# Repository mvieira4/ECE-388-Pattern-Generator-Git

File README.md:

# ECE-388-Pattern-Generator-Git
Demo https://youtu.be/JeO_5P8q-XI

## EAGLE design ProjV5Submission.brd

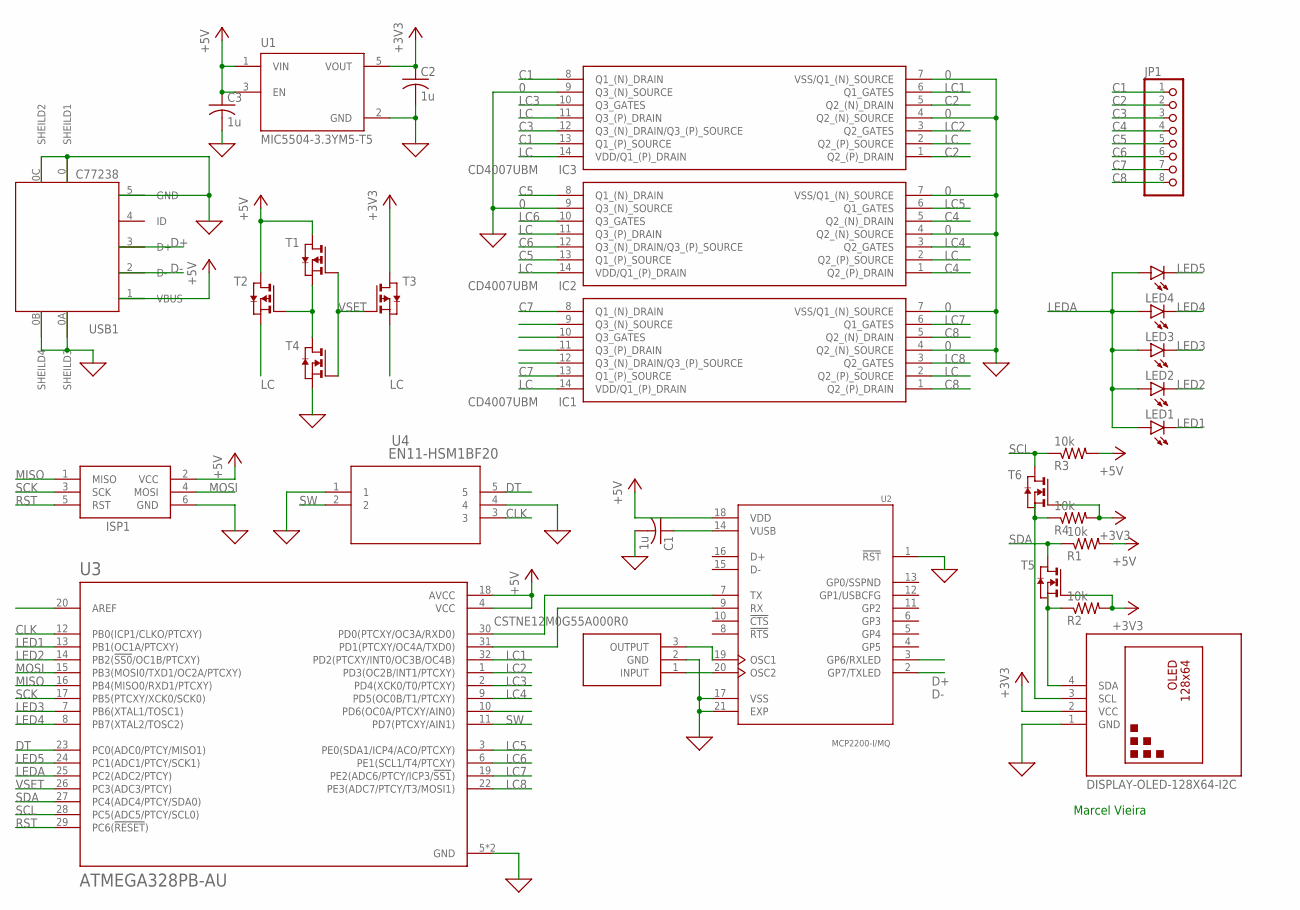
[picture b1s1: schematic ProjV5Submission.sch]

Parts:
C1, C2, C3: 1u; C0805
IC1, IC2, IC3: CD4007UBM; SOIC127P600X175-14N
ISP1: AVRISP-6; AVRISP
JP1: PINHD-1X8-3.5MM; 1X08-3.5MM
LED1, LED2, LED3, LED4, LED5: LEDCHIP-LED0805; CHIP-LED0805
R1, R2, R3, R4: 10k; R0805
T1, T2, T3: PMOSSOT23; SOT-23
T4, T5, T6: NMOSSOT23; SOT-23
U1: MIC5504-3.3YM5-T5; SOT95P280X145-5N
U2: MCP2200-I/MQ; QFN65P500X500X100-21N
U3: ATMEGA328PB-AU; QFP80P900X900X120-32N
U4: EN11-HSM1BF20; EN11-HSM_TTE
U$1: DISPLAY-OLED-128X64-I2C
USB1: C77238
Y1: CSTNE12M0G55A000R0

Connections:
0: C1.2, C2.2, C3.2, IC1.4 (Q2_(N)_SOURCE), IC1.7 (VSS/Q1_(N)_SOURCE), IC2.4 (Q2_(N)_SOURCE), IC2.7 (VSS/Q1_(N)_SOURCE), IC2.9 (Q3_(N)_SOURCE), IC3.4 (Q2_(N)_SOURCE), IC3.7 (VSS/Q1_(N)_SOURCE), IC3.9 (Q3_(N)_SOURCE), ISP1.6 (GND), T4.2 (S), U1.2 (GND), U2.1 (!RST), U2.17 (VSS), U2.21 (EXP), U3.5 (GND), U3.21 (GND), U4.1, U4.4, U$1.1 (GND), USB1.0 (SHEILD1), USB1.0A (SHEILD3), USB1.0B (SHEILD4), USB1.0C (SHEILD2), USB1.5 (GND), Y1.2 (GND)
+3V3: C2.1, R2.2, R4.2, T3.1 (D), T5.3 (G), T6.3 (G), U1.5 (VOUT), U$1.2 (VCC)
+5V: C3.1, ISP1.2 (VCC), R1.2, R3.2, T1.1 (D), T2.1 (D), U1.1 (VIN), U1.3 (EN), U2.18 (VDD), U3.4 (VCC), U3.18 (AVCC), USB1.1 (VBUS)
C1: IC3.8 (Q1_(N)_DRAIN), IC3.13 (Q1_(P)_SOURCE), JP1.1
C2: IC3.1 (Q2_(P)_DRAIN), IC3.5 (Q2_(N)_DRAIN), JP1.2
C3: IC3.12 (Q3_(N)_DRAIN/Q3_(P)_SOURCE), JP1.3
C4: IC2.1 (Q2_(P)_DRAIN), IC2.5 (Q2_(N)_DRAIN), JP1.4
C5: IC2.8 (Q1_(N)_DRAIN), IC2.13 (Q1_(P)_SOURCE), JP1.5
C6: IC2.12 (Q3_(N)_DRAIN/Q3_(P)_SOURCE), JP1.6
C7: IC1.8 (Q1_(N)_DRAIN), IC1.13 (Q1_(P)_SOURCE), JP1.7
C8: IC1.1 (Q2_(P)_DRAIN), IC1.5 (Q2_(N)_DRAIN), JP1.8
CLK: U3.12 (PB0(ICP1/CLKO/PTCXY)), U4.3
D+: U2.3 (GP6/RXLED), USB1.3 (D+)
D-: U2.2 (GP7/TXLED), USB1.2 (D-)
DT: U3.23 (PC0(ADC0/PTCY/MISO1)), U4.5
LC: IC1.2 (Q2_(P)_SOURCE), IC1.14 (VDD/Q1_(P)_DRAIN), IC2.2 (Q2_(P)_SOURCE), IC2.11 (Q3_(P)_DRAIN), IC2.14 (VDD/Q1_(P)_DRAIN), IC3.2 (Q2_(P)_SOURCE), IC3.11 (Q3_(P)_DRAIN), IC3.14 (VDD/Q1_(P)_DRAIN), T2.2 (S), T3.2 (S)
LC1: IC3.6 (Q1_GATES), U3.32 (PD2(PTCXY/INT0/OC3B/OC4B))
LC2: IC3.3 (Q2_GATES), U3.1 (PD3(OC2B/INT1/PTCXY))
LC3: IC3.10 (Q3_GATES), U3.2 (PD4(XCK0/T0/PTCXY))
LC4: IC2.3 (Q2_GATES), U3.9 (PD5(OC0B/T1/PTCXY))
LC5: IC2.6 (Q1_GATES), U3.3 (PE0(SDA1/ICP4/ACO/PTCXY))
LC6: IC2.10 (Q3_GATES), U3.6 (PE1(SCL1/T4/PTCXY))
LC7: IC1.6 (Q1_GATES), U3.19 (PE2(ADC6/PTCY/ICP3/!SS1!))
LC8: IC1.3 (Q2_GATES), U3.22 (PE3(ADC7/PTCY/T3/MOSI1))
LED1: LED1.C, U3.13 (PB1(OC1A/PTCXY))
LED2: LED2.C, U3.14 (PB2(!SS0!/OC1B/PTCXY))
LED3: LED3.C, U3.7 (PB6(XTAL1/TOSC1))
LED4: LED4.C, U3.8 (PB7(XTAL2/TOSC2))
LED5: LED5.C, U3.24 (PC1(ADC1/PTCY/SCK1))
LEDA: LED1.A, LED2.A, LED3.A, LED4.A, LED5.A, U3.25 (PC2(ADC2/PTCY))
MISO: ISP1.1 (MISO), U3.16 (PB4(MISO0/RXD1/PTCXY))
MOSI: ISP1.4 (MOSI), U3.15 (PB3(MOSI0/TXD1/OC2A/PTCXY))
unnamed: U2.19 (OSC1), Y1.3 (OUTPUT)
unnamed: C1.1, U2.14 (VUSB)
unnamed: T1.2 (S), T2.3 (G), T4.1 (D)
unnamed: U2.7 (TX), U3.30 (PD0(PTCXY/OC3A/RXD0))
unnamed: U2.9 (RX), U3.31 (PD1(PTCXY/OC4A/TXD0))
unnamed: U2.20 (OSC2), Y1.1 (INPUT)
unnamed: R2.1, T5.2 (S), U$1.4 (SDA)
unnamed: R4.1, T6.2 (S), U$1.3 (SCL)
RST: ISP1.5 (RST), U3.29 (PC6(!RESET!))
SCK: ISP1.3 (SCK), U3.17 (PB5(PTCXY/XCK0/SCK0))
SCL: R3.1, T6.1 (D), U3.28 (PC5(ADC5/PTCY/SCL0))
SDA: R1.1, T5.1 (D), U3.27 (PC4(ADC4/PTCY/SDA0))
SW: U3.11 (PD7(PTCXY/AIN1)), U4.2
VSET: T1.3 (G), T3.3 (G), T4.3 (G), U3.26 (PC3(ADC3/PTCY))

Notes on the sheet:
Marcel Vieira

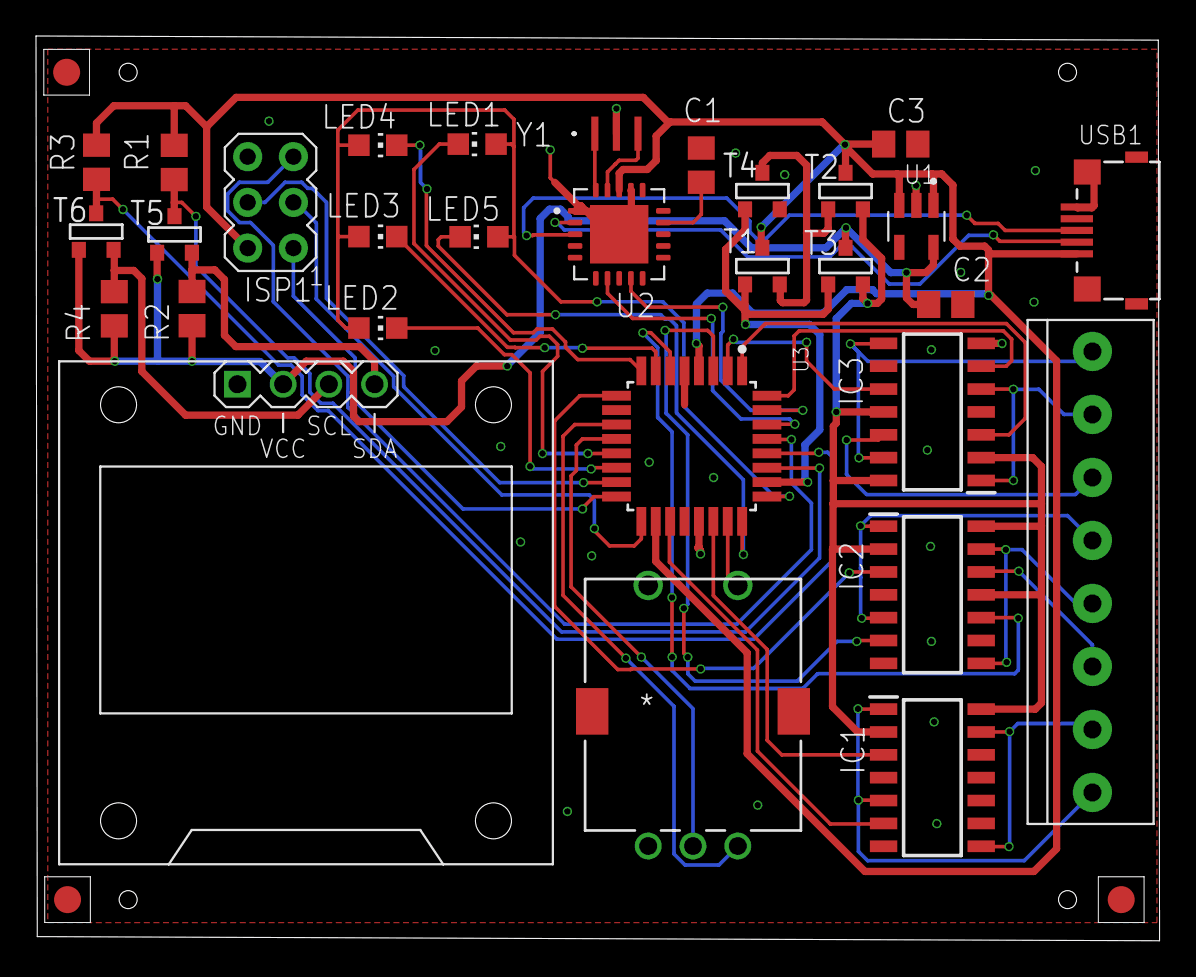
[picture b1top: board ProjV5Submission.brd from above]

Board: 2 copper layers, 62.4 x 50.3 mm, 33 parts (0 on the bottom side), 46 nets.

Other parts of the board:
U$2, U$3, U$4: FIDUCIAL_G15S

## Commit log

2020-11-09 Adding All Resources
2020-11-09 Schematic Changes
    Added votage and ground flags and switched to running board at 3.3V
2020-11-09 Cleared Random Files
2020-11-09 Reordered Dir
    Got rid of Eagle dir
2020-11-10 Updated schematic and pdf
    Switched serial chip to run on 3.3V and updated the pdf file
2020-11-10 Update Schematic
    Changed the foot print for the rotary encoder to the EN11-HSM1BF20
2020-11-11 Updated Board Layout and Cam filse
    Rerouted wires to make board smaller
2020-11-11 Updated Schematic and Layout
    Removed all errors on both
2020-11-11 Updated Cam Files
    Made sure cam files were up to date
2020-11-11 Reorganized Repository
    Removed junk files
2020-11-11 Updated Layout
    Add silkscreen labels and fixed silk screen issues
2020-11-11 Updated Cam Files and PDF
    Made sure cam files and pdf were up to date
2020-11-12 Updated Schematic
    Added power flags has issues with flag at output of the voltage regulator
2020-11-12 Update Schematic
    Labels Deleted
2020-11-13 Updated Schematic
    Fixed usb, made power source changes, got rid of missing part error relayed out board
2020-11-18 Updated Gerbers
    Spoke with Jin to clear up miss understanding of how to process cam files
2020-11-18 Updated Gerbers
    Reuploaded incase of erros
2020-11-19 Added to report
2020-11-19 Added copies of old versions
    Updated version numbers and add old versions for comparison and report writing
2020-11-24 Updated Layout
    Added holes to board and moved usb over
2020-11-30 Added Assembly Files
    Added assembly file and BOM
2020-11-30 Update In Case of Missed Changes
2020-11-30 Renamed Files
    Renamed some files ran more checks and fixed format up some more
2020-11-30 Renamed Every Thing
2020-11-30 Redundant Update
2020-12-08 Final Report Submission
2020-12-08 Resubmittion of Report
2020-12-08 Final Submission

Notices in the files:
parts and their libraries:
diy-modules: Released under the Creative Commons Attribution 4.0 International License: http://creativecommons.org/licenses/by/4.0
dicons: Copyright (C) 2004, Bob Starr (rtzaudio@mindspring.com)
